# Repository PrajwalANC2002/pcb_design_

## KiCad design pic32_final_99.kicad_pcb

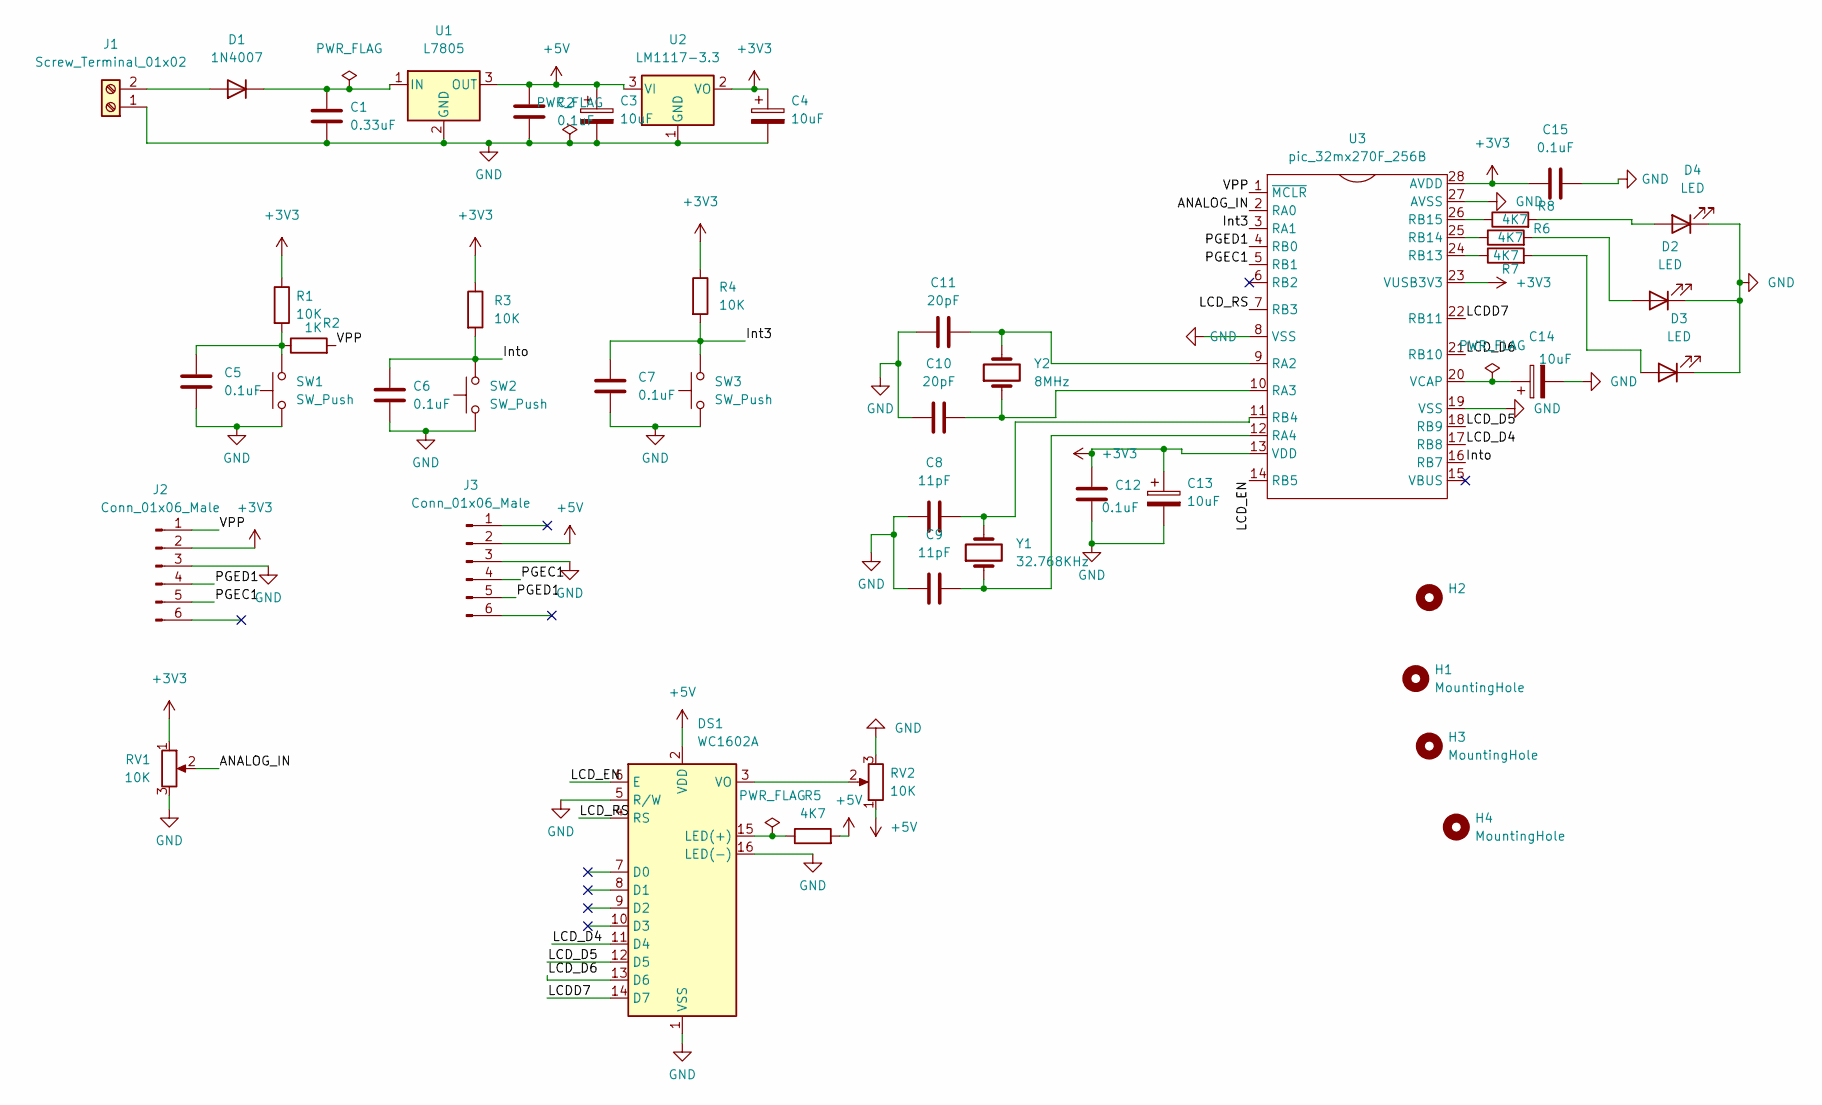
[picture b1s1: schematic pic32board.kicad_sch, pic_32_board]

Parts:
C1: 0.33uF; C_Disc_D4.3mm_W1.9mm_P5.00mm
C2, C5, C6, C7, C12, C15: 0.1uF; C_Disc_D4.3mm_W1.9mm_P5.00mm
C3, C4, C13, C14: 10uF; CP_Radial_D4.0mm_P1.50mm
C8, C9: 11pF; C_Disc_D4.3mm_W1.9mm_P5.00mm
C10, C11: 20pF; C_Disc_D4.3mm_W1.9mm_P5.00mm
D1: 1N4007; D_DO-41_SOD81_P10.16mm_Horizontal
D2, D3, D4: LED; LED_D5.0mm
DS1: WC1602A
H1, H3, H4: MountingHole
H2: (no value)
J1: Screw_Terminal_01x02; TerminalBlock_Altech_AK300-2_P5.00mm
J2: Conn_01x06_Male; PinHeader_1x06_P2.54mm_Vertical
J3: Conn_01x06_Male; PinHeader_1x06_P2.54mm_Horizontal
R1, R3, R4: 10K; R_Axial_DIN0309_L9.0mm_D3.2mm_P12.70mm_Horizontal
R2: 1K; R_Axial_DIN0309_L9.0mm_D3.2mm_P12.70mm_Horizontal
R5, R6, R7, R8: 4K7; R_Axial_DIN0309_L9.0mm_D3.2mm_P12.70mm_Horizontal
RV1, RV2: 10K; Potentiometer_ACP_CA9-H5_Horizontal
SW1, SW2, SW3: SW_Push; SW_TH_Tactile_Omron_B3F-10xx
U1: L7805; TO-220-3_Horizontal_TabDown
U2: LM1117-3.3; TO-220-3_Horizontal_TabDown
U3: pic_32mx270F_256B; DIP-28_W7.62mm_LongPads
Y1: 32.768KHz; Crystal_DS26_D2.0mm_L6.0mm_Vertical
Y2: 8MHz; Crystal_HC18-U_Vertical

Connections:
+3V3: C4.1, C12.2, C13.1, C15.1, J2.2, R1.1, R3.1, R4.1, RV1.1, U2.2 (VO), U3.13 (VDD), U3.23 (VUSB3V3), U3.28 (AVDD)
+5V: C2.1, C3.1, DS1.2 (VDD), J3.2, R5.2, RV2.1, U1.3 (OUT), U2.3 (VI)
/ANALOG_IN: RV1.2, U3.2 (RA0)
/Int3: C7.1, R4.2, SW3.2, U3.3 (RA1)
/Into: C6.1, R3.2, SW2.2, U3.16 (RB7)
/LCDD7: DS1.14 (D7), U3.22 (RB11)
/LCD_D4: DS1.11 (D4), U3.17 (RB8)
/LCD_D5: DS1.12 (D5), U3.18 (RB9)
/LCD_D6: DS1.13 (D6), U3.21 (RB10)
/LCD_EN: DS1.6 (E), U3.14 (RB5)
/LCD_RS: DS1.4 (RS), U3.7 (RB3)
/PGEC1: J2.5, J3.4, U3.5 (RB1)
/PGED1: J2.4, J3.5, U3.4 (RB0)
/VPP: J2.1, R2.2, U3.1 (~MCLR)
GND: C1.2, C2.2, C3.2, C4.2, C5.2, C6.2, C7.2, C8.1, C9.1, C10.2, C11.1, C12.1, C13.2, C14.2, C15.2, D2.1 (K), D3.1 (K), D4.1 (K), DS1.1 (VSS), DS1.5 (R/W), DS1.16 (LED(-)), J1.1, J2.3, J3.3, RV1.3, RV2.3, SW1.1, SW2.1, SW3.1, U1.2 (GND), U2.1 (GND), U3.8 (VSS), U3.19 (VSS), U3.27 (AVSS)
unnamed: C1.1, D1.1 (K), U1.1 (IN)
unnamed: C5.1, R1.2, R2.1, SW1.2
unnamed: C8.2, U3.11 (RB4), Y1.2
unnamed: C9.2, U3.12 (RA4), Y1.1
unnamed: C10.1, U3.10 (RA3), Y2.1
unnamed: C11.2, U3.9 (RA2), Y2.2
unnamed: C14.1, U3.20 (VCAP)
unnamed: D1.2 (A), J1.2
unnamed: D2.2 (A), R6.2
unnamed: D3.2 (A), R7.2
unnamed: D4.2 (A), R8.2
unnamed: DS1.3 (VO), RV2.2
unnamed: DS1.15 (LED(+)), R5.1
unnamed: R6.1, U3.25 (RB14)
unnamed: R7.1, U3.24 (RB13)
unnamed: R8.1, U3.26 (RB15)

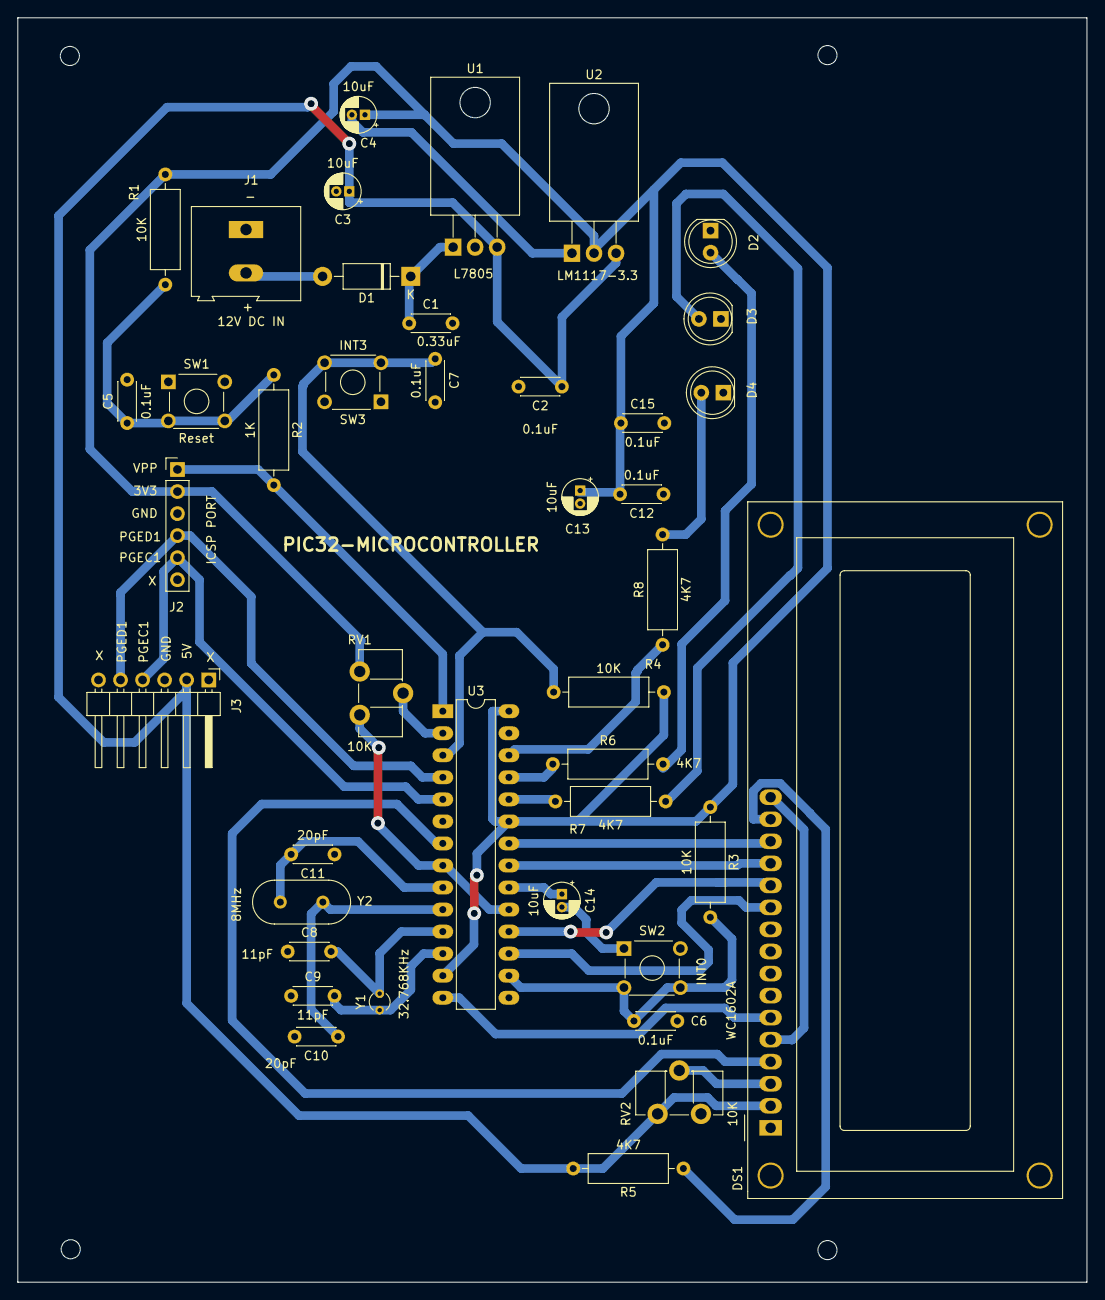
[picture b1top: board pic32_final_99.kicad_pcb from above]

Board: 2 copper layers, 123.2 x 145.7 mm, 45 parts (0 on the bottom side), 31 nets.

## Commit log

2023-08-29 Add files via upload
    pic32mx270f256b
